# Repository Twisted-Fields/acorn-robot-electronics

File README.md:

# Acorn Robot Electronics

### About

PCBs designed in Kicad for Acorn the farming robot.

Our dream is that you will fab your own boards, make changes, and share your work - giving this design life beyond our efforts.

Designed by Taylor Alexander for Twisted Fields, for the Acorn Precision Farming Rover.

Many thanks to [Daniel Theobald](https://www.twistedfields.com/blog). Without your financial support and encouragement this project would not have been possible.

Thanks to all of our supporters on Open Collective. Your contributions are helping grow this project in to a sustainable open source organization.

You can support this project yourself at our [Open Collective Page](https://opencollective.com/twisted-fields-research-collective).

To learn more about Acorn, please see our [announcement blog post](https://community.twistedfields.com/t/introducing-acorn-a-precision-farming-rover-from-twisted-fields/).
Or see a more recent [technical update here](https://community.twistedfields.com/t/march-2022-update-simulation-brakes-funding-and-navigation-improvements/202).

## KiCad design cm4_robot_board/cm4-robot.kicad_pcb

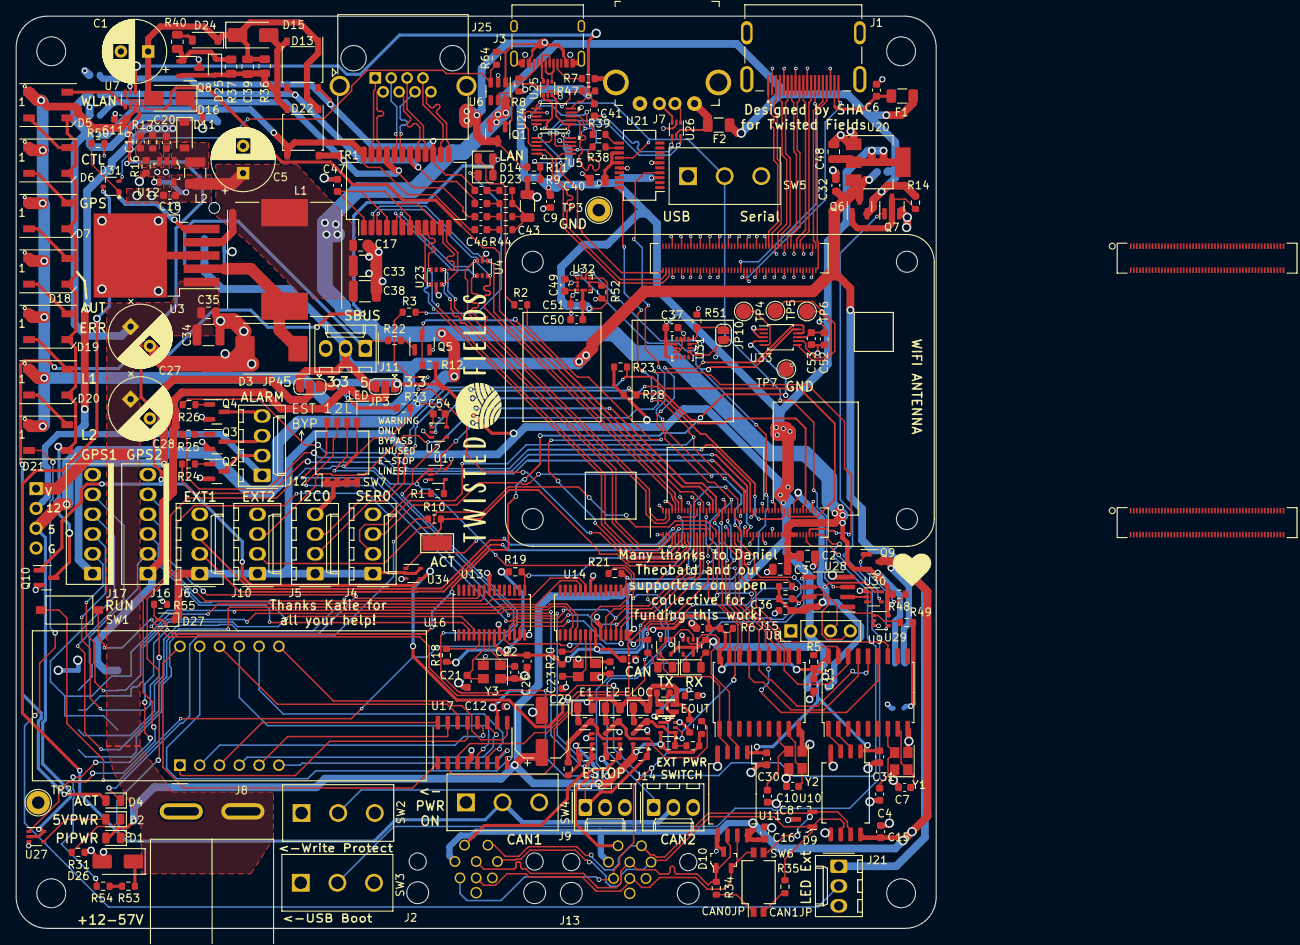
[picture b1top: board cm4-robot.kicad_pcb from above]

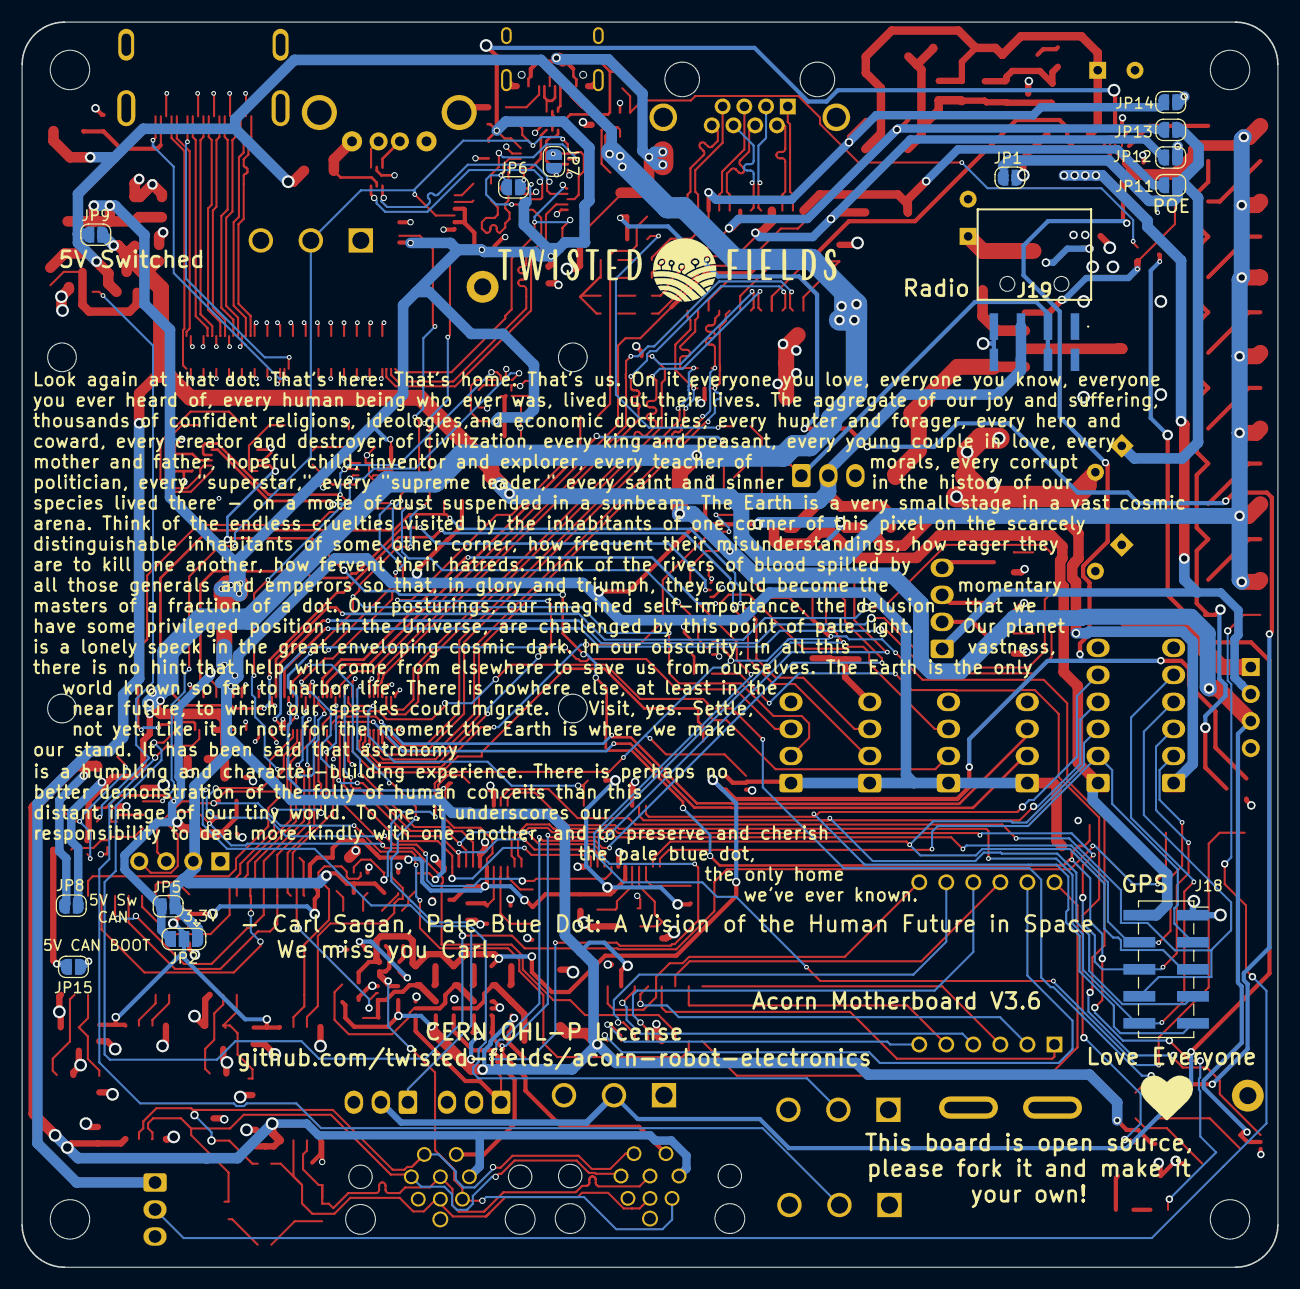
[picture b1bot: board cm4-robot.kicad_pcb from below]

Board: 4 copper layers, 118.0 x 117.0 mm, 262 parts (14 on the bottom side), 223 nets.

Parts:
C1, C27, C28: 47uF 63V solid; CP_Radial_D8.0mm_P3.50mm
C2, C3, C17, C48: 10uF 25V; C_0805_2012Metric
C4, C7, C8, C10: 18pF 50V; C_0603_1608Metric
C5: 1000uF 10v solid; CP_Radial_D8.0mm_P3.50mm
C6, C9, C11, C12, C13, C14, C15, C16, C25, C26, C30, C31, C36, C37, C41, C47, C49, C50, C53, C54: 0.1uF 50V; C_0603_1608Metric
C18: 4.7uF 25V; C_0603_1608Metric
C19, C21, C22, C23, C24: 22pF 50V; C_0603_1608Metric
C20: 1uF 25V; C_0603_1608Metric
C29: 470uF 10V; CP_Elec_6.3x7.7
C32, C51, C52: 1uF 50V; C_0603_1608Metric
C33, C38: 47uF 16V; C_1210_3225Metric
C34: 4.7uF 100V; C_1210_3225Metric
C35, C39: 0.1uF 100V; C_0805_2012Metric
C40: 0.1uF 50V; C_0805_2012Metric
C42, C44, C45, C46: 22nF 100v; C_0603_1608Metric
C43: 1nF 2kV; C_1206_3216Metric
D1, D17, D23: LED_YELLOW; LED_0805_2012Metric
D2, D8, D28, D29: LED_RED; LED_0805_2012Metric
D3: D_Schottky; D_SMC
D4, D12, D14: LED_GREEN; LED_0805_2012Metric
D5, D6, D7, D18, D19, D20, D21: WS2812B; LED_WS2812B_PLCC4_5.0x5.0mm_P3.2mm
D9, D10: CDSOT23-SM712; SOT-23-3
D11: MBR0530; D_SOD-123
D13, D22: ABS2; Diode_Bridge_Diotec_ABS
D15: SMAJ60A; D_SMA
D16: D; D_SMA
D24: 28V / 500mW; D_SOD-123
D25: 15V / 200mW; D_SOD-323
D26: SMAJ51A; D_SMA
D27: 1N4148WS; D_SOD-323
D30: LED_Dual_KKAA; LED-ARRAY-SMD_4P-L1.9-W1.6-BL-CW
D31: Diode Dual Common Cathode 80v maximum reverse vol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; SOT-323_SC-70
F1, F2: Polyfuse; Fuse_1206_3216Metric
H1, H2, H3, H4: MountingHole; MountingHole_3.7mm
J1: 1747981-1; TE_1747981-1
J2: CAN Interface A; M12A-08PFFR
J3: USB_C_Receptacle_USB2.0; USB_C_Receptacle_XKB_U262-16XN-4BVC11
J4, J5, J6, J10, J12: Conn_01x04; Molex_KK-254_AE-6410-04A_1x04_P2.54mm_Vertical
J7: USB HOSTING OUT; USB_A_Female_UE27AC54100
J8: Conn_01x02; PowerPole_PP45_1336G1_1x2_Horizontal
J9: ESTOP; Molex_KK-254_AE-6410-03A_1x03_P2.54mm_Vertical
J11, J21: Conn_01x03; Molex_KK-254_AE-6410-03A_1x03_P2.54mm_Vertical
J13: CAN Interface B; M12A-08PFFR
J14: Power Sw; Molex_KK-254_AE-6410-03A_1x03_P2.54mm_Vertical
J15: I2C OLED; PinHeader_1x04_P2.54mm_Vertical
J16, J17: Ckmtw-W-2510S06P_1x06_P2.54mm_Vertical
J18: Serial Rear; PinSocket_2x05_P2.54mm_Vertical_SMD
J19: SBUS; 610108249221
J22: DNP; PinHeader_1x04_P2.54mm_Vertical
J23, J24: Conn_01x01; DF40C-100DS-0.4V51
J25: RJ45; RJ45_R-RJ45R08P-B000
JP1, JP5, JP6, JP7, JP8, JP9, JP10, JP11, JP12, JP13, JP14, JP15: SolderJumper_2_Open; SolderJumper-2_P1.3mm_Open_RoundedPad1.0x1.5mm
JP2, JP3, JP4: SolderJumper_3_Open; SolderJumper-3_P1.3mm_Open_RoundedPad1.0x1.5mm
L1: 100uH; L_15mmx15mm
L2: 10uH; L_1210_3225Metric
Module1: ComputeModule4-CM4; Raspberry-Pi-4-Compute-Module
Q1: Q_PMOS_GSD; SOT-23
Q2, Q3, Q4, Q5, Q10: Q_NMOS_GSD; SOT-23
Q6, Q9: AO3401A; SOT-23
Q7: AO3400A; SOT-23
Q8: Si2328DS; SOT-23-3
R1, R10, R19, R21: 1k; R_0603_1608Metric
R2, R3: 470R; R_0603_1608Metric
R4, R9, R11, R32, R56, R57: 2.2k 1%; R_0603_1608Metric
R5, R6, R12, R14, R18, R20, R23, R28, R29, R30, R33, R47, R48, R49, R58, R61, R62, R63, R64: 10K; R_0603_1608Metric
R7, R8, R51, R52: 5.1k; R_0603_1608Metric
R13, R38, R39: 27R; R_0603_1608Metric
R15: 56R; R_0603_1608Metric
R16: 205k; R_0603_1608Metric
R17: 1.8M; R_0603_1608Metric
R22, R24, R25, R26: 100R; R_0603_1608Metric
R27, R45, R46, R59, R60: 130R; R_0603_1608Metric
R31: 200R; R_0603_1608Metric
R34, R35: 120R; R_0603_1608Metric
R36: 24k; R_0805_2012Metric
R37: 249k; R_0805_2012Metric
R40: 51k; R_0805_2012Metric
R41, R42, R43, R44: 75R 100v; R_0603_1608Metric
R50: 100k; R_0603_1608Metric
R53, R54: 50k 0.1%; R_0603_1608Metric
R55: 5.1k 0.1%; R_0603_1608Metric
SW1: B3U-1000P; SW_TS_1101_C_W
SW2, SW3, SW4, SW5: SW_SPDT; CS12ANW03
SW6: SW_DIP_x02; SW_DIP_SPSTx02_Slide_KingTek_DSHP02TS_W7.62mm_P1.27mm
SW7: CONFIG_SW; SW_DIP_SPSTx04_Slide_KingTek_DSHP04TS_W7.62mm_P1.27mm
TP1: TestPoint; TestPoint_Keystone_5019_Minature
TP2, TP3: TestPoint; TestPoint_Loop_D2.60mm_Drill1.6mm_Beaded
TP4, TP5, TP6, TP7: TestPoint; TestPoint_Pad_D2.0mm
TR1: G2401CG; Transformer_Ethernet_YDS_30F-51NL_SO-24_7.1x15.1mm
U1, U2, U15, U18, U19, U22, U27, U29, U30, U34, U35, U36: SN74LVC1G07QDCKTQ1; SOT-353_SC-70-5
U3: LM2576HVS-5; TO-263-5_TabPin3
U4, U23: TPD4E1U06DCKR; SOT-363_SC-70-6
U5, U24: ISL54222AIUZ
U6: LTC4412xS6; TSOT-23-6
U7: TXS0101DCKR; SOT-363_SC-70-6
U8, U9: MCP2515-xSO; SOIC-18W_7.5x11.6mm_P1.27mm
U10, U11: isolator; SOIC-8_7.5x5.85mm_P1.27mm
U12: TPS61040DBVR; SOT-753
U13, U14: SC16IS752; TSSOP-28_4.4x9.7mm_P0.65mm
U16: CC56-12SEKWA; CA56-12SEKWA
U17: ET6226M; SO-16_3.9x9.9mm_P1.27mm
U20: TLV1117LV33DCYR; SOT-223-3_TabPin2
U21: FT231XS; SSOP-20_3.9x8.7mm_P0.635mm
U25, U26: USBLC6-2P6; SOT-666
U28: PCA9536D; SOIC-8_3.9x4.9mm_P1.27mm
U31: LSM6DS3; LGA-14_3x2.5mm_P0.5mm_LayoutBorder3x4y
U32: LIS3MDL; LGA-12_2x2mm_P0.5mm
U33: ADS1115IDGS; TSSOP-10_3x3mm_P0.5mm
Y1, Y2: 16MHz; Crystal_SMD_3225-4Pin_3.2x2.5mm
Y3, Y4: 14.7456MHz; Crystal_SMD_3225-4Pin_3.2x2.5mm

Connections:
3.3V_5V_PI_CONTROL: U28.2 (IO1), U30.2 (A)
3.3V_PI_OUT: C36.1, JP2.3 (B), JP5.1 (A), Module1.86 (+3.3v_(Output)), R29.1, R30.1, U28.8 (VDD), U30.5 (VCC)
5V_CAN_ENABLE: R49.1, U28.1 (IO0), U29.1 (/OE)
5V_switched: C11.1, C32.1, D5.1 (VDD), D6.1 (VDD), D7.1 (VDD), D18.1 (VDD), D19.1 (VDD), D20.1 (VDD), D21.1 (VDD), J11.2, J19.5, J19.6, J21.1, JP3.3 (B), JP4.3 (B), JP9.2 (B), Q6.3 (D), U7.6 (VCCB), U20.3 (VI)
5V_switched_CAN: C15.2, C16.2, J2.7, J13.7, JP8.2 (B), Q9.3 (D), U10.8 (VCC2), U11.8 (VCC2)
+3V3: C9.2, C12.1, C29.1, C37.1, C40.1, C41.2, C48.1, C50.1, C51.1, C52.2, C53.1, D1.2 (A), D27.1 (K), J4.1, J5.1, J6.1, J10.1, J15.2, JP2.1 (A), JP3.1 (A), JP4.1 (A), JP5.2 (B), JP10.1 (A), Module1.78 (GPIO_VREF(1.8v/3.3v_Input)), R4.2, R12.1, R13.1, R15.1, R23.1, R28.1, R32.2, R33.1, R47.1, R56.2, R57.2, R61.1, R62.1, R63.1, U1.5 (VCC), U5.10 (VDD), U7.1 (VCCA), U15.5 (VCC), U17.10 (VCC), U18.5 (VCC), U19.5 (VCC), U20.2 (VO), U21.3 (VCCIO), U21.13 (3V3OUT), U21.15 (VCC), U22.5 (VCC), U24.10 (VDD), U31.5 (VDDIO), U31.8 (VDD), U31.12 (CS), U32.5 (Vdd), U32.6 (Vdd_IO), U32.10 (~CS), U33.8 (VDD), U34.2 (A), U34.5 (VCC), U35.5 (VCC), U36.5 (VCC)
+5V: C2.1, C3.1, C5.1, C17.1, C18.1, C33.1, C38.1, C54.1, F1.1, F2.2, J22.3, JP8.1 (A), JP9.1 (A), L1.2, L2.1, Module1.77 (+5v_(Input)), Module1.79 (+5v_(Input)), Module1.81 (+5v_(Input)), Module1.83 (+5v_(Input)), Module1.85 (+5v_(Input)), Module1.87 (+5v_(Input)), Q1.2 (S), Q6.2 (S), Q9.2 (S), R14.1, R48.1, U2.5 (VCC), U3.4 (FB), U6.6 (SENSE), U12.4 (EN), U12.5 (VIN), U27.2 (A), U27.5 (VCC), U29.5 (VCC)
+12V: C19.1, C20.1, D11.1 (K), J12.1, J22.2, R17.2
/5V_FUSED: F2.1, J7.1 (VBUS), U26.5 (VBUS)
/CAN0_N: D10.1 (Input), J2.8, J13.8, R34.1, U11.6 (CANL)
/CAN0_P: D10.2 (Input), J2.5, J13.5, SW6.4, U11.7 (CANH)
/CAN1_N: D9.1 (Input), J2.3, J13.3, R35.1, U10.6 (CANL)
/CAN1_P: D9.2 (Input), J2.2, J13.2, SW6.3, U10.7 (CANH)
/D0N: J25.2, TR1.22 (MX1-)
/D0P: J25.1, TR1.23 (MX1+)
/D1N: J25.6, TR1.19 (MX2-)
/D1P: J25.3, TR1.20 (MX2+)
/D2N: J25.5, TR1.16 (MX3-)
/D2P: J25.4, TR1.17 (MX3+)
/D3N: J25.8, TR1.13 (MX4-)
/D3P: J25.7, TR1.14 (MX4+)
/ESTOP_SINK_ALL: R27.2, R57.1, R63.2, U35.4 (Y), U36.1 (/OE)
/HDMI0_CEC: J1.13 (CEC), Module1.151 (HDMI0_CEC)
/HDMI0_CK_N: J1.12 (CK-), Module1.190 (HDMI0_CLK_N)
/HDMI0_CK_P: J1.10 (CK+), Module1.188 (HDMI0_CLK_P)
/HDMI0_D0_N: J1.9 (D0-), Module1.184 (HDMI0_TX0_N)
/HDMI0_D0_P: J1.7 (D0+), Module1.182 (HDMI0_TX0_P)
/HDMI0_D1_N: J1.6 (D1-), Module1.178 (HDMI0_TX1_N)
/HDMI0_D1_P: J1.4 (D1+), Module1.176 (HDMI0_TX1_P)
/HDMI0_D2_N: J1.3 (D2-), Module1.172 (HDMI0_TX2_N)
/HDMI0_D2_P: J1.1 (D2+), Module1.170 (HDMI0_TX2_P)
/HDMI0_HOTPLUG: J1.19 (HPD/HEAC-), Module1.153 (HDMI0_HOTPLUG)
/HDMI0_SCL: J1.15 (SCL), Module1.200 (HDMI0_SCL)
/HDMI0_SDA: J1.16 (SDA), Module1.199 (HDMI0_SDA)
/HDMI_5v: C6.1, F1.2, J1.18 (+5V)
/LED_3.3V_POWER_NONINV: D8.2 (A), D28.2 (A), D29.2 (A), D30.3 (A1), Q10.1 (G), R58.2, U7.5 (OE), U34.4 (Y)
/LED_3.3V_POWER_SW: D4.2 (A), D14.2 (A), D23.2 (A)
/RX1: J16.3, J18.5, U13.4 (RXA)
/RX2: J16.5, J18.9, U13.24 (RXB)
/RX3: J17.3, J18.6, U14.4 (RXA)
/RX4: J17.5, J18.10, U14.24 (RXB)
/TX1: J16.2, J18.3, U13.3 (TXA)
/TX2: J16.4, J18.7, U13.23 (TXB)
/TX3: J17.2, J18.4, U14.3 (TXA)
/TX4: J17.4, J18.8, U14.23 (TXB)
/USB_DN: R38.2, U21.12 (USBDM)
/USB_DP: R39.2, U21.11 (USBDP)
/VMEAS: D27.2 (A), R54.2, R55.1, U33.4 (AIN0)
//LED_EN: R33.2, SW7.5, U1.1 (/OE), U18.1 (/OE), U19.1 (/OE), U27.1 (/OE), U34.1 (/OE)
/~5V_EN: D31.3 (K), J14.2, SW4.2 (B)
/~VBUS_5V_ENA: D31.2 (A), R64.1, U6.3 (CTL)
/~VIN_5V_EN: D31.1 (A), R50.2, U3.5 (~ON/OFF)
A1: Module1.54 (GPIO4), R24.1
A2: Module1.56 (GPIO3), R25.1
A3: Module1.58 (GPIO2), R26.1
CAN_CIPO: Module1.44 (GPIO10), U8.14 (SI), U9.14 (SI)
CAN_COPI: Module1.40 (GPIO9), U8.15 (SO), U9.15 (SO)
CAN_CS0: Module1.39 (GPIO8), U8.16 (~CS)
CAN_CS1: Module1.37 (GPIO7), U9.16 (~CS)
CAN_SCI0: Module1.41 (GPIO25), U8.12 (~INT)
CAN_SCI1: Module1.45 (GPIO24), U9.12 (~INT)
CAN_SCK: Module1.38 (GPIO11), U8.13 (SCK), U9.13 (SCK)
CS1: Module1.49 (GPIO18), U13.10 (A0/~CS)
CS2: Module1.50 (GPIO17), U14.10 (A0/~CS)
EEPROM_nWP: Module1.20 (EEPROM_nWP), SW2.2 (B)
ESTOP: Module1.30 (GPIO6), U36.2 (A)
ESTOP_OUT: D30.4 (A2), J2.6, J13.6, R60.2, U36.4 (Y)
ESTOP_SINK1: J2.1, R32.1, SW7.8, U22.1 (/OE)
ESTOP_SINK2: J13.1, R4.1, SW7.7, U15.1 (/OE)
ESTOP_SINK_LOCAL: J9.1, R56.1, SW7.6, U35.1 (/OE)
ETH_LEDG: Module1.17 (Ethernet_nLED2(3.3v)), R3.2
ETH_LEDY: Module1.15 (Ethernet_nLED3(3.3v)), R2.2
EXTRA_1_GPIO16: J6.2, Module1.29 (GPIO16)
EXTRA_2_GPIO12: J6.3, Module1.31 (GPIO12)
EXTRA_3_GPIO1: J10.2, Module1.35 (ID_SC)
EXTRA_4_GPIO0: J10.3, Module1.36 (ID_SD)
EXTRA_GPIO: J14.1, U28.5 (IO3)
FB: C19.2, R16.2, R17.1, U12.3 (FB)
GLOBAL_EN: Module1.99 (Global_EN), SW1.2
GND: C1.2, C2.2, C3.2, C4.2, C5.2, C6.2, C7.2, C8.2, C9.1, C10.2, C11.2, C12.2, C13.1, C14.1, C15.1, C16.1, C17.2, C18.2, C20.2, C21.1, C22.2, C23.1, C24.2, C25.1, C26.1, C27.2, C28.2, C29.2, C30.2, C31.2, C32.2, C33.2, C34.2, C35.2, C36.2, C37.2, C38.2, C40.2, C41.1, C43.2, C47.1, C48.2, C49.2, C50.2, C51.2, C52.1, C53.2, C54.2, D3.2 (A), D9.3 (Output), D10.3 (Output), D26.2 (A2), J1.2 (D2S), J1.5 (D1S), J1.8 (D0S), J1.11 (CKS), J1.17 (GND), J1.SH1 (SH), J1.SH2 (SH), J1.SH3 (SH), J1.SH4 (SH), J2.4, J2.9, J3.A1 (GND), J3.A12 (GND), J3.B1 (GND), J3.B12 (GND), J3.S1 (SHIELD), J4.4, J5.4, J6.4, J7.4 (GND), J7.SH (Shield), J8.2, J9.3, J10.4, J11.3, J13.4, J13.9, J14.3, J15.1, J16.6, J17.6, J18.1, J19.7, J19.8, J21.3, J22.4, J24.1, JP12.1 (A), JP14.1 (A), JP15.2 (B), Module1.1 (GND), Module1.2 (GND), Module1.7 (GND), Module1.8 (GND), Module1.13 (GND), Module1.14 (GND), Module1.22 (GND), Module1.23 (GND), Module1.32 (GND), Module1.33 (GND), Module1.42 (GND), Module1.43 (GND), Module1.52 (GND), Module1.53 (GND), Module1.59 (GND), Module1.60 (GND), Module1.65 (GND), Module1.66 (GND), Module1.71 (GND), Module1.74 (GND), Module1.98 (GND), Module1.107 (GND), Module1.108 (GND), Module1.113 (GND), Module1.114 (GND), Module1.119 (GND), Module1.120 (GND), Module1.125 (GND), Module1.126 (GND), Module1.131 (GND), Module1.132 (GND), Module1.137 (GND), Module1.138 (GND), Module1.144 (GND), Module1.150 (GND), Module1.155 (GND), Module1.156 (GND), Module1.161 (GND), Module1.162 (GND), Module1.167 (GND), Module1.168 (GND), Module1.173 (GND), Module1.174 (GND), Module1.179 (GND), Module1.180 (GND), Module1.185 (GND), Module1.186 (GND), Module1.191 (GND), Module1.192 (GND), Module1.197 (GND), Module1.198 (GND), Q2.2 (S), Q3.2 (S), Q4.2 (S), Q5.2 (S), Q7.2 (S), Q8.3 (D), Q10.2 (S), R7.1, R8.2, R9.2, R16.1, R31.1, R51.1, R52.1, R55.2, R58.1, R59.2, SW2.1 (A), SW3.1 (A), SW4.1 (A), SW5.1 (A), SW7.1, SW7.2, SW7.3, SW7.4, TP2.1, TP3.1, TP7.1, U1.3 (GND), U2.1 (/OE), U2.3 (GND), U3.3 (GND), U4.2 (VN), U5.5 (GND), U5.9 (*OE), U6.2 (GND), U7.2 (GND), U8.9 (VSS), U9.9 (VSS), U10.4 (GND1), U10.5 (GND2), U11.4 (GND1), U11.5 (GND2), U12.2 (GND), U13.9 (I2C/~SPI), U13.14 (SDA/VSS), U13.22 (VSS), U14.9 (I2C/~SPI), U14.14 (SDA/VSS), U14.22 (VSS), U15.3 (GND), U17.4 (GND), U18.3 (GND), U19.3 (GND), U20.1 (GND), U21.6 (GND), U21.16 (GND), U22.2 (A), U22.3 (GND), U23.2 (VN), U24.5 (GND), U24.9 (*OE), U25.2 (GND), U26.2 (GND), U27.3 (GND), U28.4 (VSS), U29.2 (A), U29.3 (GND), U30.1 (/OE), U30.3 (GND), U31.2 (SDX), U31.3 (SCX), U31.6 (GND), U31.7 (GND), U32.2 (GND), U32.3 (GND), U32.12 (GND), U33.1 (ADDR), U33.3 (GND), U34.3 (GND), U35.3 (GND), U36.3 (GND), Y1.2, Y1.4, Y2.2, Y2.4, Y3.2, Y3.4, Y4.2, Y4.4
GR1: U16.12 (CC1), U17.1 (GR1)
GR2: U16.9 (CC2), U17.5 (GR2)
GR3: U16.8 (CC3), U17.6 (GR3)
GR4: U16.6 (CC4), U17.7 (GR4)
IRQ1: Module1.24 (GPIO26), R19.1, U13.15 (~IRQ)
IRQ2: Module1.48 (GPIO27), R21.1, U14.15 (~IRQ)
KP: U16.3 (DPX), U17.16 (DP/KP)
KS1: U16.11 (a), U17.8 (SG1/KS1)
KS2: U16.7 (b), U17.9 (SG2/KS2)
KS3: U16.4 (c), U17.11 (SG3/KS3)
KS4: U16.2 (d), U17.12 (SG4/KS4)
KS5: U16.1 (e), U17.13 (SG5/KS5)
KS6: U16.10 (f), U17.14 (SG6/KS6)
KS7: U16.5 (g), U17.15 (SG7/KS7)
unnamed: C42.2, R41.1
unnamed: C43.1, R41.2, R42.2, R43.2, R44.2
unnamed: C44.2, R42.1
unnamed: C45.2, R43.1
unnamed: C46.2, R44.1
unnamed: C47.2, TR1.1 (CT), TR1.4 (CT), TR1.7 (CT), TR1.10 (CT)
unnamed: D1.1 (K), R1.1
unnamed: D2.2 (A), U27.4 (Y)
unnamed: D2.1 (K), R31.2
unnamed: D3.1 (K), L1.1, U3.2 (OUT)
unnamed: D4.1 (K), R10.2
unnamed: D5.4 (DIN), U7.4 (B)
unnamed: D5.2 (DOUT), D6.4 (DIN)
unnamed: D6.2 (DOUT), D7.4 (DIN)
unnamed: D8.1 (K), R27.1
unnamed: D11.2 (A), L2.2, U12.1 (SW)
unnamed: D12.2 (A), R13.2
unnamed: D12.1 (K), U18.4 (Y)
unnamed: D14.1 (K), R2.1
unnamed: D16.1 (K), JP1.1 (A)
unnamed: D17.2 (A), R15.2
unnamed: D17.1 (K), U19.4 (Y)
unnamed: D7.2 (DOUT), D18.4 (DIN)
unnamed: D18.2 (DOUT), D19.4 (DIN)
unnamed: D5.3 (VSS), D6.3 (VSS), D7.3 (VSS), D18.3 (VSS), D19.3 (VSS), D20.3 (VSS), D21.3 (VSS), Q10.3 (D)
unnamed: D19.2 (DOUT), D20.4 (DIN)
unnamed: D20.2 (DOUT), D21.4 (DIN)
unnamed: D21.2 (DOUT), J21.2
unnamed: D23.1 (K), R3.1
unnamed: D24.2 (A), R40.2
unnamed: D25.1 (K), Q8.1 (G), R37.2, R40.1
unnamed: D28.1 (K), R45.1
unnamed: D29.1 (K), R46.1
unnamed: D30.1 (K1), R59.1
unnamed: D30.2 (K2), R60.1
unnamed: J3.A5 (CC1), R7.2
unnamed: J3.B5 (CC2), R8.1
unnamed: J12.2, Q2.3 (D)
unnamed: J12.3, Q3.3 (D)
unnamed: J12.4, Q4.3 (D)
unnamed: JP10.2 (B), R51.2, U31.1 (SDO/SA0)
unnamed: JP15.1 (A), R49.2
unnamed: Q1.1 (G), U6.5 (GATE)
unnamed: Q2.1 (G), R24.2
unnamed: Q3.1 (G), R25.2
unnamed: Q4.1 (G), R26.2
unnamed: Q5.1 (G), R22.2
unnamed: Q6.1 (G), Q7.3 (D), R14.2
unnamed: Q7.1 (G), U30.4 (Y)
unnamed: Q9.1 (G), R48.2, U29.4 (Y)
unnamed: R34.2, SW6.1
unnamed: R35.2, SW6.2
unnamed: R53.2, R54.1
unnamed: R1.2, U1.4 (Y)
unnamed: SW1.1, U2.4 (Y)
unnamed: C10.1, U8.8 (OSC1), Y2.1
unnamed: C8.1, U8.7 (OSC2), Y2.3
unnamed: R6.1, U8.17 (~RESET)
unnamed: C7.1, U9.8 (OSC1), Y1.1
unnamed: C4.1, U9.7 (OSC2), Y1.3
unnamed: R5.1, U9.17 (~RESET)
unnamed: U9.2 (RXCAN), U10.2 (RXD)
unnamed: U9.1 (TXCAN), U10.3 (TXD)
unnamed: C21.2, U13.6 (XTAL1), Y3.3
unnamed: C22.1, U13.7 (XTAL2), Y3.1
unnamed: R18.1, U13.5 (~RESET)
unnamed: C23.2, U14.6 (XTAL1), Y4.3
unnamed: C24.1, U14.7 (XTAL2), Y4.1
unnamed: R20.1, U14.5 (~RESET)
unnamed: R46.2, R61.2, U15.2 (A), U22.4 (Y)
unnamed: R45.2, R62.2, U15.4 (Y), U35.2 (A)
unnamed: C49.1, U32.4 (C1)
unnamed: R52.2, U32.9 (SDO/SA1)
unnamed: TP4.1, U33.5 (AIN1)
unnamed: TP5.1, U33.6 (AIN2)
unnamed: TP6.1, U33.7 (AIN3)
PI_n_LED_ACT: Module1.21 (PI_nLED_Activity), R10.1, TP1.1
RC_SBUS: J11.1, J19.3, J19.4, R22.1
RUN_PG: Module1.92 (RUN_PG), U2.2 (A)
RXLED: U8.2 (RXCAN), U11.2 (RXD), U19.2 (A)
RX_GPIO15: J4.2, Module1.51 (GPIO15), U21.20 (TXD)
SBUS_RX: Module1.34 (GPIO5), Q5.3 (D), R12.2
SCL0_GPIO45: J5.2, Module1.80 (SCL0), R28.2
SCL6: J15.3, Module1.47 (GPIO23), R29.2, U17.2 (CLK), U28.6 (SCL), U31.13 (SCL), U32.1 (SCL/SPC), U33.10 (SCL)
SDA0_GPIO44: J5.3, Module1.82 (SDA0), R23.2
SDA6: J15.4, Module1.46 (GPIO22), R30.2, U17.3 (DAT), U28.7 (SDA), U31.14 (SDA), U32.11 (SDA/SDI/SDO), U33.9 (SDA)
SERIALPWR1: J16.1, J18.2, JP3.2 (C)
SERIALPWR2: J17.1, JP4.2 (C)
SERIAL_CAN_PWR_3.3V: C13.2, C14.2, C25.2, C26.2, C30.1, C31.1, JP2.2 (C), R5.2, R6.2, R18.2, R19.2, R20.2, R21.2, U8.18 (VDD), U9.18 (VDD), U10.1 (VCC1), U11.1 (VCC1), U13.8 (VDD), U14.8 (VDD)
SERIAL_CIPO: Module1.26 (GPIO19), U13.12 (SO), U14.12 (SO)
SERIAL_CLK: Module1.25 (GPIO21), U13.13 (SCL/SCLK), U14.13 (SCL/SCLK)
SERIAL_COPI: Module1.27 (GPIO20), U13.11 (A1/SI), U14.11 (A1/SI)
SER_SELECT: R47.2, SW5.2 (B), U21.14 (~RESET), U24.1 (SEL), U28.3 (IO2)
TRD0_N: Module1.10 (Ethernet_Pair0_N), TR1.3 (TD1-), U4.6 (CH4)
TRD0_P: Module1.12 (Ethernet_Pair0_P), TR1.2 (TD1+), U4.1 (CH1)
TRD1_N: Module1.6 (Ethernet_Pair1_N), TR1.6 (TD2-), U4.3 (CH2)
TRD1_P: Module1.4 (Ethernet_Pair1_P), TR1.5 (TD2+), U4.4 (CH3)
TRD2_N: Module1.9 (Ethernet_Pair2_N), TR1.9 (TD3-), U23.6 (CH4)
TRD2_P: Module1.11 (Ethernet_Pair2_P), TR1.8 (TD3+), U23.1 (CH1)
TRD3_N: Module1.5 (Ethernet_Pair3_N), TR1.12 (TD4-), U23.3 (CH2)
TRD3_P: Module1.3 (Ethernet_Pair3_P), TR1.11 (TD4+), U23.4 (CH3)
TXLED: U8.1 (TXCAN), U11.3 (TXD), U18.2 (A)
TX_GPIO14: J4.3, Module1.55 (GPIO14), U21.4 (RXD)
USBAP_D_N: U5.8 (HSD1-), U26.6 (I/O1)
USBAP_D_P: U5.2 (HSD1+), U26.4 (I/O2)
USBA_D_N: J7.2 (D-), U26.1 (I/O1)
USBA_D_P: J7.3 (D+), U26.3 (I/O2)
USBCP_D_N: JP6.2 (B), U24.6 (D-), U25.3 (I/O2)
USBCP_D_P: JP7.2 (B), U24.4 (D+), U25.1 (I/O1)
USBC_D_N: J3.A7 (D-), J3.B7 (D-), U25.4 (I/O2)
USBC_D_P: J3.A6 (D+), J3.B6 (D+), U25.6 (I/O1)
USBC_VBUS_IN: J3.A4 (VBUS), J3.A9 (VBUS), J3.B4 (VBUS), J3.B9 (VBUS), Q1.3 (D), R11.1, R64.2, U6.1 (VIN), U25.5 (VBUS)
USB_N: Module1.103 (USB2_N), U5.6 (D-)
USB_OTG: Module1.101 (USB_OTG_ID), R9.1, R11.2, U5.1 (SEL)
USB_P: Module1.105 (USB2_P), U5.4 (D+)
USB_SERIAL_D+: R39.1, U24.3 (HSD2+)
USB_SERIAL_D-: R38.1, U24.7 (HSD2-)
USB_SW_D+: JP7.1 (A), U5.3 (HSD2+), U24.2 (HSD1+)
USB_SW_D-: JP6.1 (A), U5.7 (HSD2-), U24.8 (HSD1-)
VC1: C46.1, D22.3, JP11.2 (B), TR1.24 (CT)
VC2: C45.1, D22.4, JP12.2 (B), TR1.21 (CT)
VC3: C44.1, D13.3, JP13.2 (B), TR1.18 (CT)
VC4: C42.1, D13.4, JP14.2 (B), TR1.15 (CT)
VMOT: C27.1, C28.1, C34.1, C35.1, D26.1 (A1), J8.1, J22.1, JP1.2 (B), JP11.1 (A), JP13.1 (A), R50.1, R53.1, U3.1 (VIN)
VOUTN: C39.2, D13.2 (-), D15.2 (A2), D22.2 (-), D25.2 (A), Q8.2 (S), R36.1, R37.1
VOUTP: C1.1, C39.1, D13.1 (+), D15.1 (A1), D16.2 (A), D22.1 (+), D24.1 (K), R36.2
WS2812: Module1.28 (GPIO13), U7.3 (A)
nPWR_LED: Module1.95 (nPI_LED_PWR), U1.2 (A)
nRPI_BOOT: Module1.93 (nRPIBOOT), SW3.2 (B)

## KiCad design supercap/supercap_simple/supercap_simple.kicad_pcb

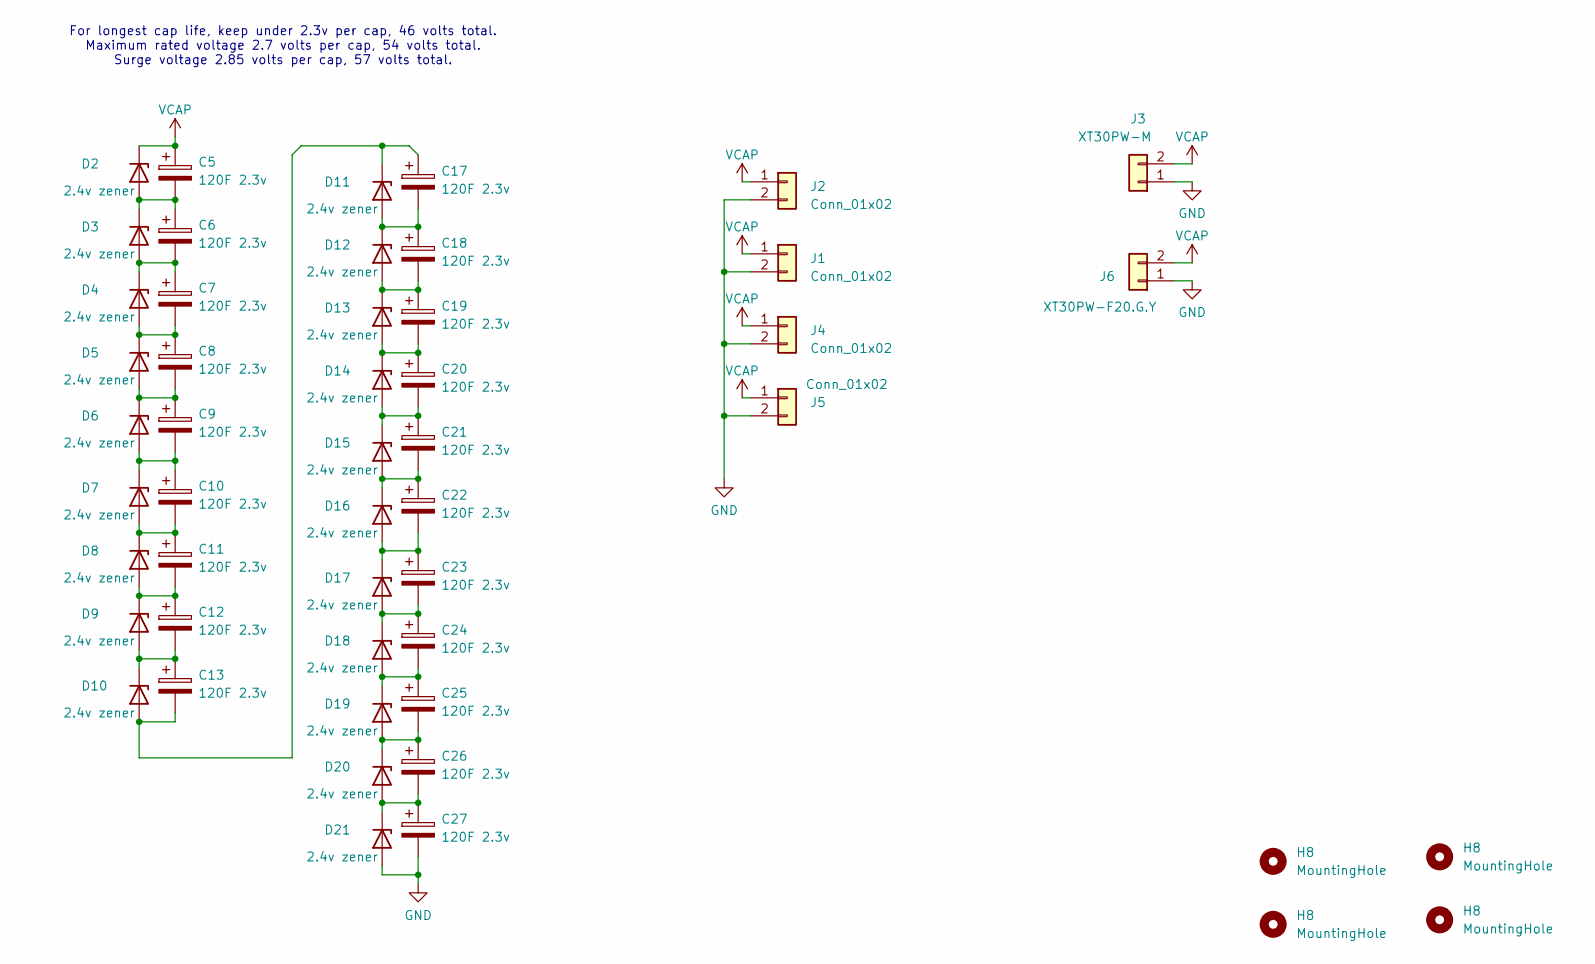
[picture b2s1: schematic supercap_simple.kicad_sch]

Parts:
C5, C6, C7, C8, C9, C10, C11, C12, C13, C17, C18, C19, C20, C21, C22, C23, C24, C25, C26, C27: 120F 2.3v; CP_Radial_D18.0mm_P7.50mm; Digikey 2085-TPLH-2R7/120WR18X60-ND
D2, D3, D4, D5, D6, D7, D8, D9, D10, D11, D12, D13, D14, D15, D16, D17, D18, D19, D20, D21: 2.4v zener; DIO_PESD5V0S1UL_315; LCSC C551192
H8: MountingHole; MountingHole_3.9mm_Plastite_#6
J1, J2, J4, J5: Conn_01x02; PowerPole_PP45_1336G1_1x2_Horizontal
J3: XT30PW-M; AMASS_XT30PW-M_1x02_P2.50mm_Horizontal; LCSC C431092
J6: XT30PW-F20.G.Y; AMASS_XT30PW-F_1x02_P2.50mm_Horizontal; LCSC C2913282

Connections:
GND: C27.2, D21.2 (A), J1.2, J2.2, J3.1, J4.2, J5.2, J6.1
unnamed: C5.2, C6.1, D2.2 (A), D3.1 (K)
unnamed: C6.2, C7.1, D3.2 (A), D4.1 (K)
unnamed: C7.2, C8.1, D4.2 (A), D5.1 (K)
unnamed: C8.2, C9.1, D5.2 (A), D6.1 (K)
unnamed: C9.2, C10.1, D6.2 (A), D7.1 (K)
unnamed: C10.2, C11.1, D7.2 (A), D8.1 (K)
unnamed: C11.2, C12.1, D8.2 (A), D9.1 (K)
unnamed: C13.2, C17.1, D10.2 (A), D11.1 (K)
unnamed: C12.2, C13.1, D9.2 (A), D10.1 (K)
unnamed: C17.2, C18.1, D11.2 (A), D12.1 (K)
unnamed: C18.2, C19.1, D12.2 (A), D13.1 (K)
unnamed: C19.2, C20.1, D13.2 (A), D14.1 (K)
unnamed: C20.2, C21.1, D14.2 (A), D15.1 (K)
unnamed: C21.2, C22.1, D15.2 (A), D16.1 (K)
unnamed: C22.2, C23.1, D16.2 (A), D17.1 (K)
unnamed: C23.2, C24.1, D17.2 (A), D18.1 (K)
unnamed: C24.2, C25.1, D18.2 (A), D19.1 (K)
unnamed: C25.2, C26.1, D19.2 (A), D20.1 (K)
unnamed: C26.2, C27.1, D20.2 (A), D21.1 (K)
VCAP: C5.1, D2.1 (K), J1.1, J2.1, J3.2, J4.1, J5.1, J6.2

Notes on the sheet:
For longest cap life, keep under 2.3v per cap, 46 volts total. Maximum rated voltage 2.7 volts per cap, 54 volts total. Surge voltage 2.85 volts per cap, 57 volts total.

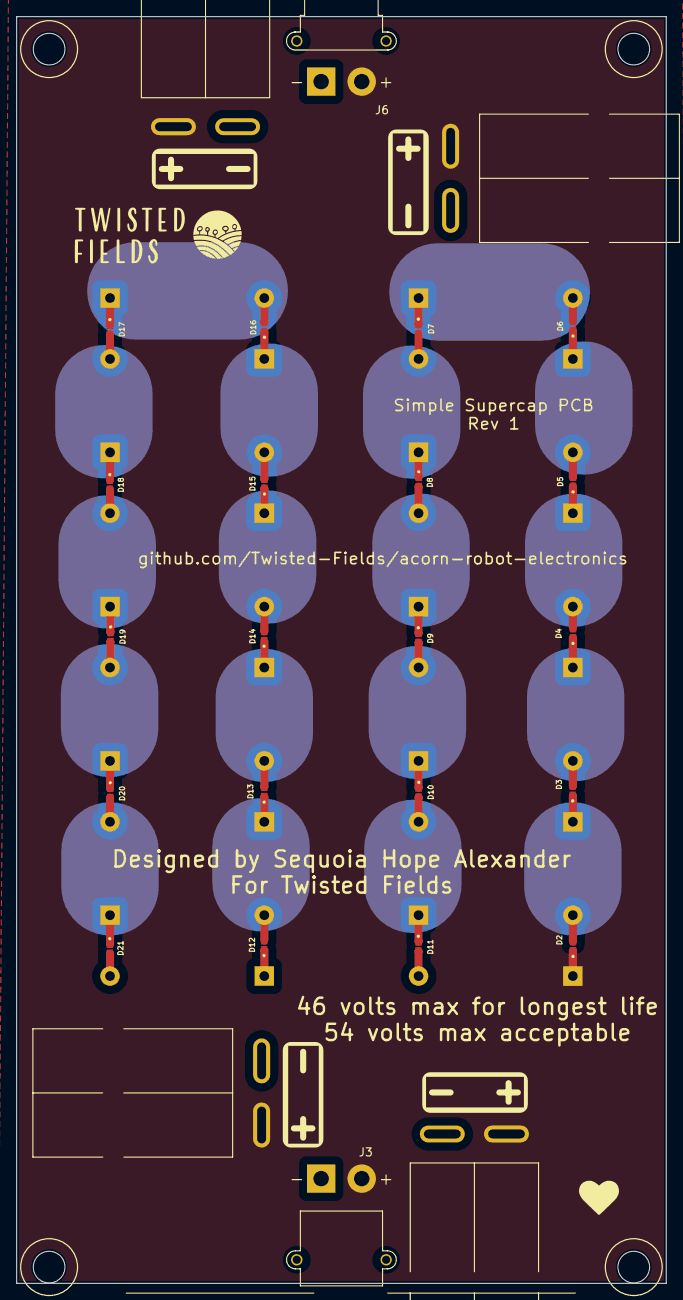
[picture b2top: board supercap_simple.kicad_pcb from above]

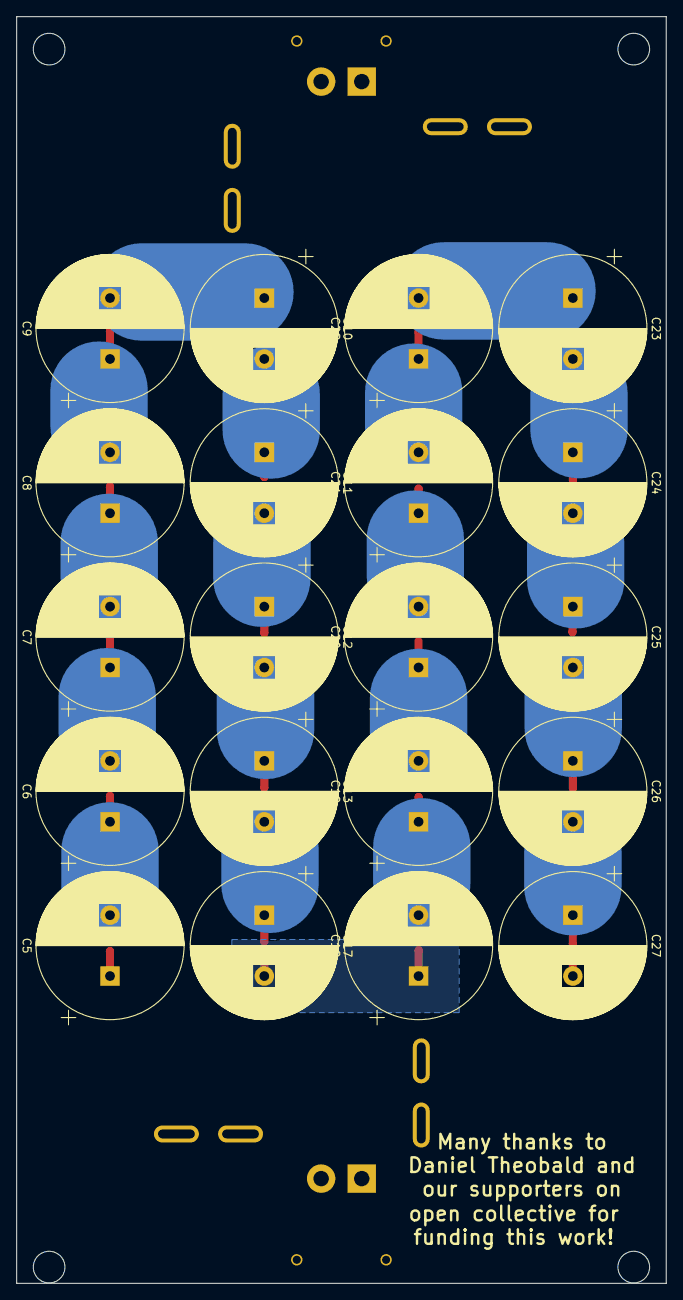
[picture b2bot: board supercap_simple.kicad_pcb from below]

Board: 4 copper layers, 80.0 x 156.0 mm, 50 parts (20 on the bottom side), 21 nets.

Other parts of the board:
H1, H2, H3, H4: MountingHole; MountingHole_3.9mm_Plastite_#6

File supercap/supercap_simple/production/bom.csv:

Designator,Footprint,Quantity,Value,LCSC Part #
"C10, C11, C12, C13, C17, C18, C19, C20, C21, C22, C23, C24, C25, C26, C27, C5, C6, C7, C8, C9",CP_Radial_D18.0mm_P7.50mm,20,120F 2.3v,
"D10, D11, D12, D13, D14, D15, D16, D17, D18, D19, D2, D20, D21, D3, D4, D5, D6, D7, D8, D9",DIO_PESD5V0S1UL_315,20,2.4v zener,C551192
"J1, J2, J4, J5",PowerPole_PP45_1336G1_1x2_Horizontal,4,Conn_01x02,
J3,AMASS_XT30PW-M_1x02_P2.50mm_Horizontal,1,XT30PW-M,C431092
J6,AMASS_XT30PW-F_1x02_P2.50mm_Horizontal,1,    XT30PW-F20.G.Y,C2913282

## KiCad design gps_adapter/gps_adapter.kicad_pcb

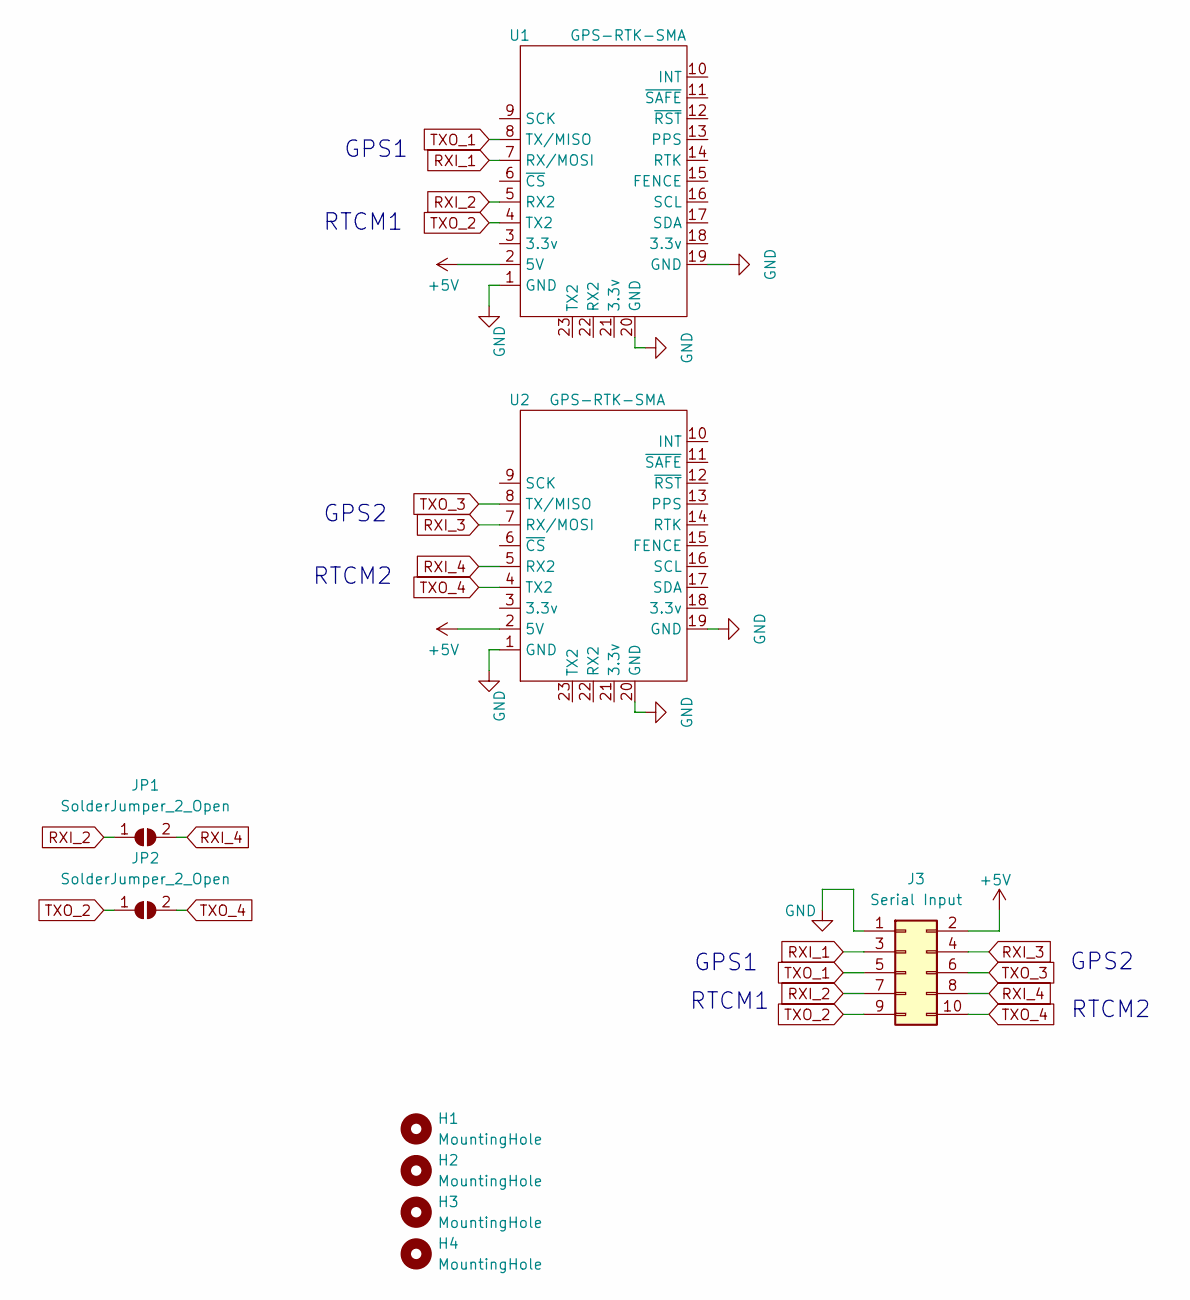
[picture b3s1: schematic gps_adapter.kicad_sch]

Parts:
H1, H2, H3, H4: MountingHole; MountingHole_3.7mm
J3: Serial Input; PinHeader_2x05_P2.54mm_Vertical
JP1, JP2: SolderJumper_2_Open; SolderJumper-2_P1.3mm_Open_RoundedPad1.0x1.5mm
U1, U2: GPS-RTK-SMA

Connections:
+5V: J3.2, U1.2 (5V), U2.2 (5V)
GND: J3.1, U1.1 (GND), U1.19 (GND), U1.20 (GND), U2.1 (GND), U2.19 (GND), U2.20 (GND)
RXI_1: J3.3, U1.7 (RX/MOSI)
RXI_2: J3.7, JP1.1 (A), U1.5 (RX2)
RXI_3: J3.4, U2.7 (RX/MOSI)
RXI_4: J3.8, JP1.2 (B), U2.5 (RX2)
TXO_1: J3.5, U1.8 (TX/MISO)
TXO_2: J3.9, JP2.1 (A), U1.4 (TX2)
TXO_3: J3.6, U2.8 (TX/MISO)
TXO_4: J3.10, JP2.2 (B), U2.4 (TX2)

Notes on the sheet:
GPS2
GPS1
RTCM2
RTCM1

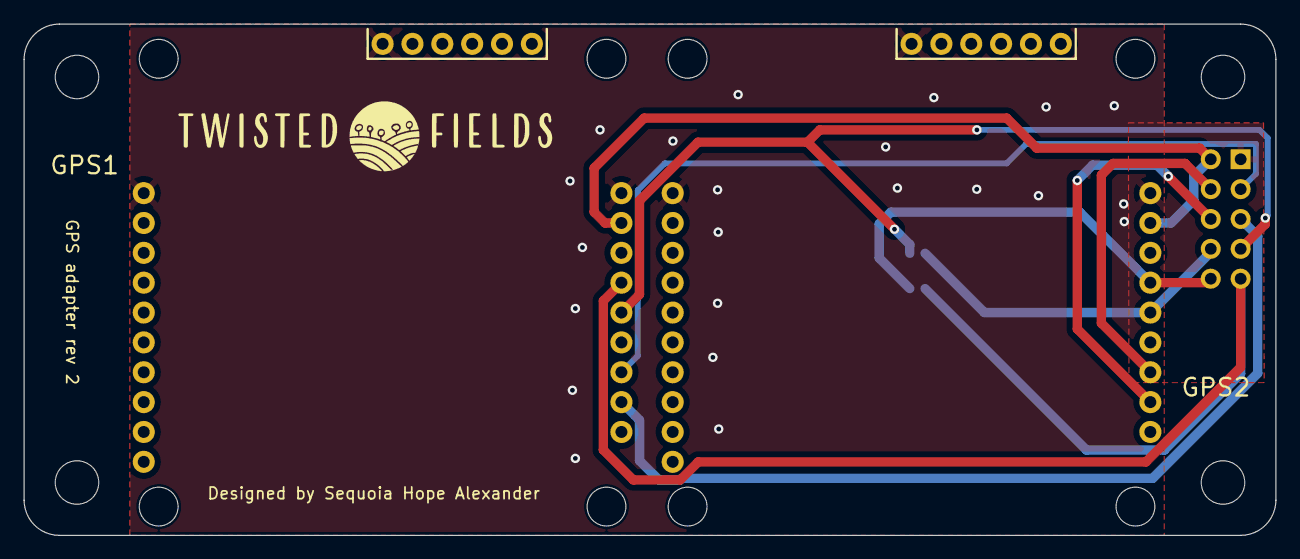
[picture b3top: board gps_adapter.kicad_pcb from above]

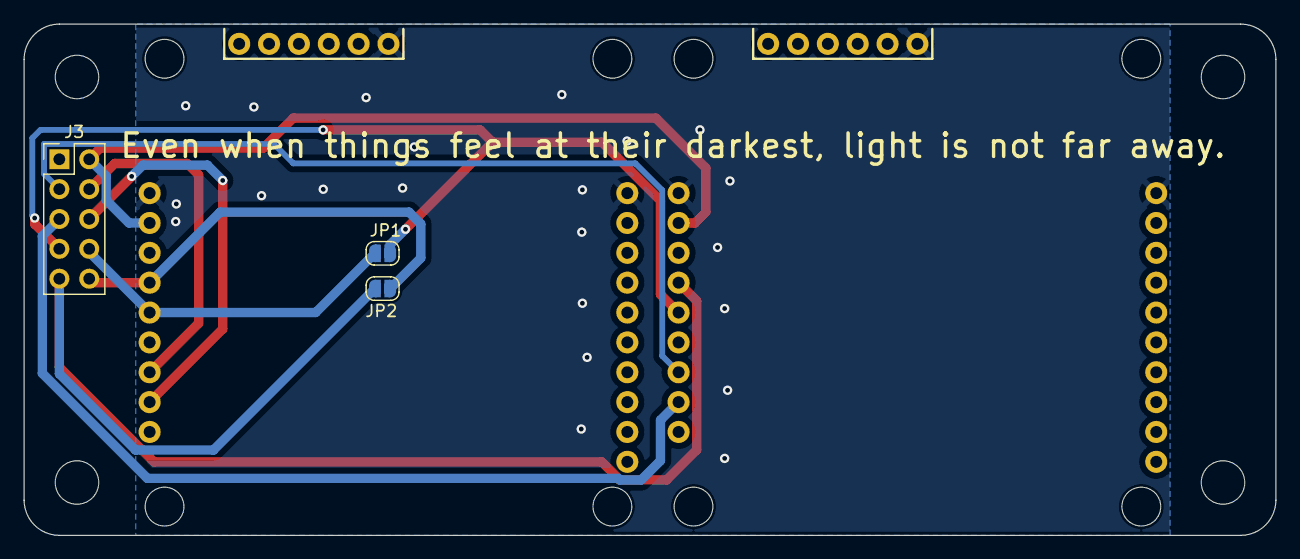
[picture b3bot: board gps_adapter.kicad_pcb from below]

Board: 2 copper layers, 106.5 x 43.5 mm, 9 parts (3 on the bottom side), 10 nets.

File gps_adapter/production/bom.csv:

Designator,Footprint,Quantity,Value,LCSC Part #
"H1, H2, H3, H4",MountingHole_3.7mm,4,MountingHole,
J3,PinHeader_2x05_P2.54mm_Vertical,1,Serial Input,
"JP1, JP2",SolderJumper-2_P1.3mm_Open_RoundedPad1.0x1.5mm,2,SolderJumper_2_Open,
"U1, U2",GPS-RTK-SMA,2,GPS-RTK-SMA,

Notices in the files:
cm4_robot_board/cm4-robot.kicad_pcb:
CERN OHL-P License
parts and their libraries:
Copyright 2021 Accelerated Designs. All rights reserved.
